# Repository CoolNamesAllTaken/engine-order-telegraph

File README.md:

# engine-order-telegraph
Ding! More doot, please.

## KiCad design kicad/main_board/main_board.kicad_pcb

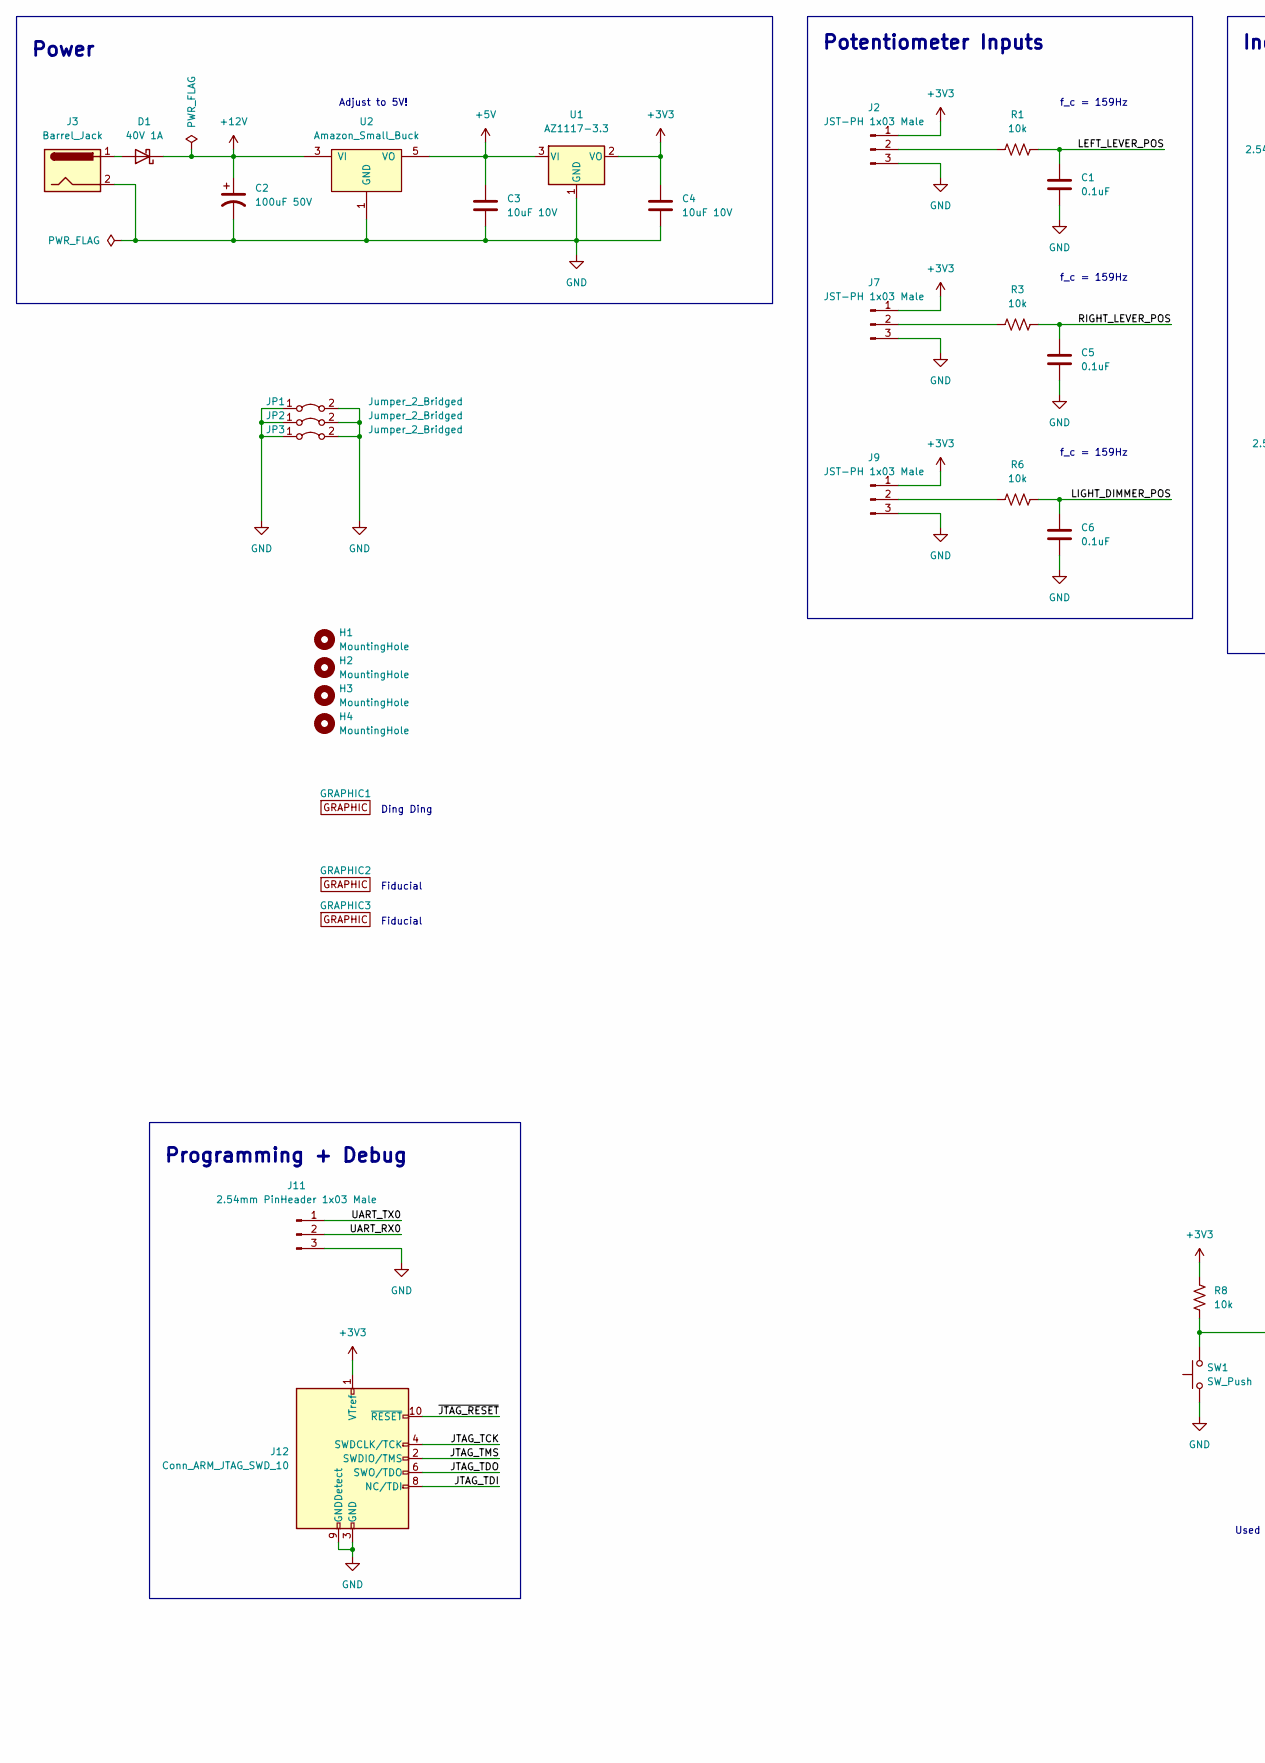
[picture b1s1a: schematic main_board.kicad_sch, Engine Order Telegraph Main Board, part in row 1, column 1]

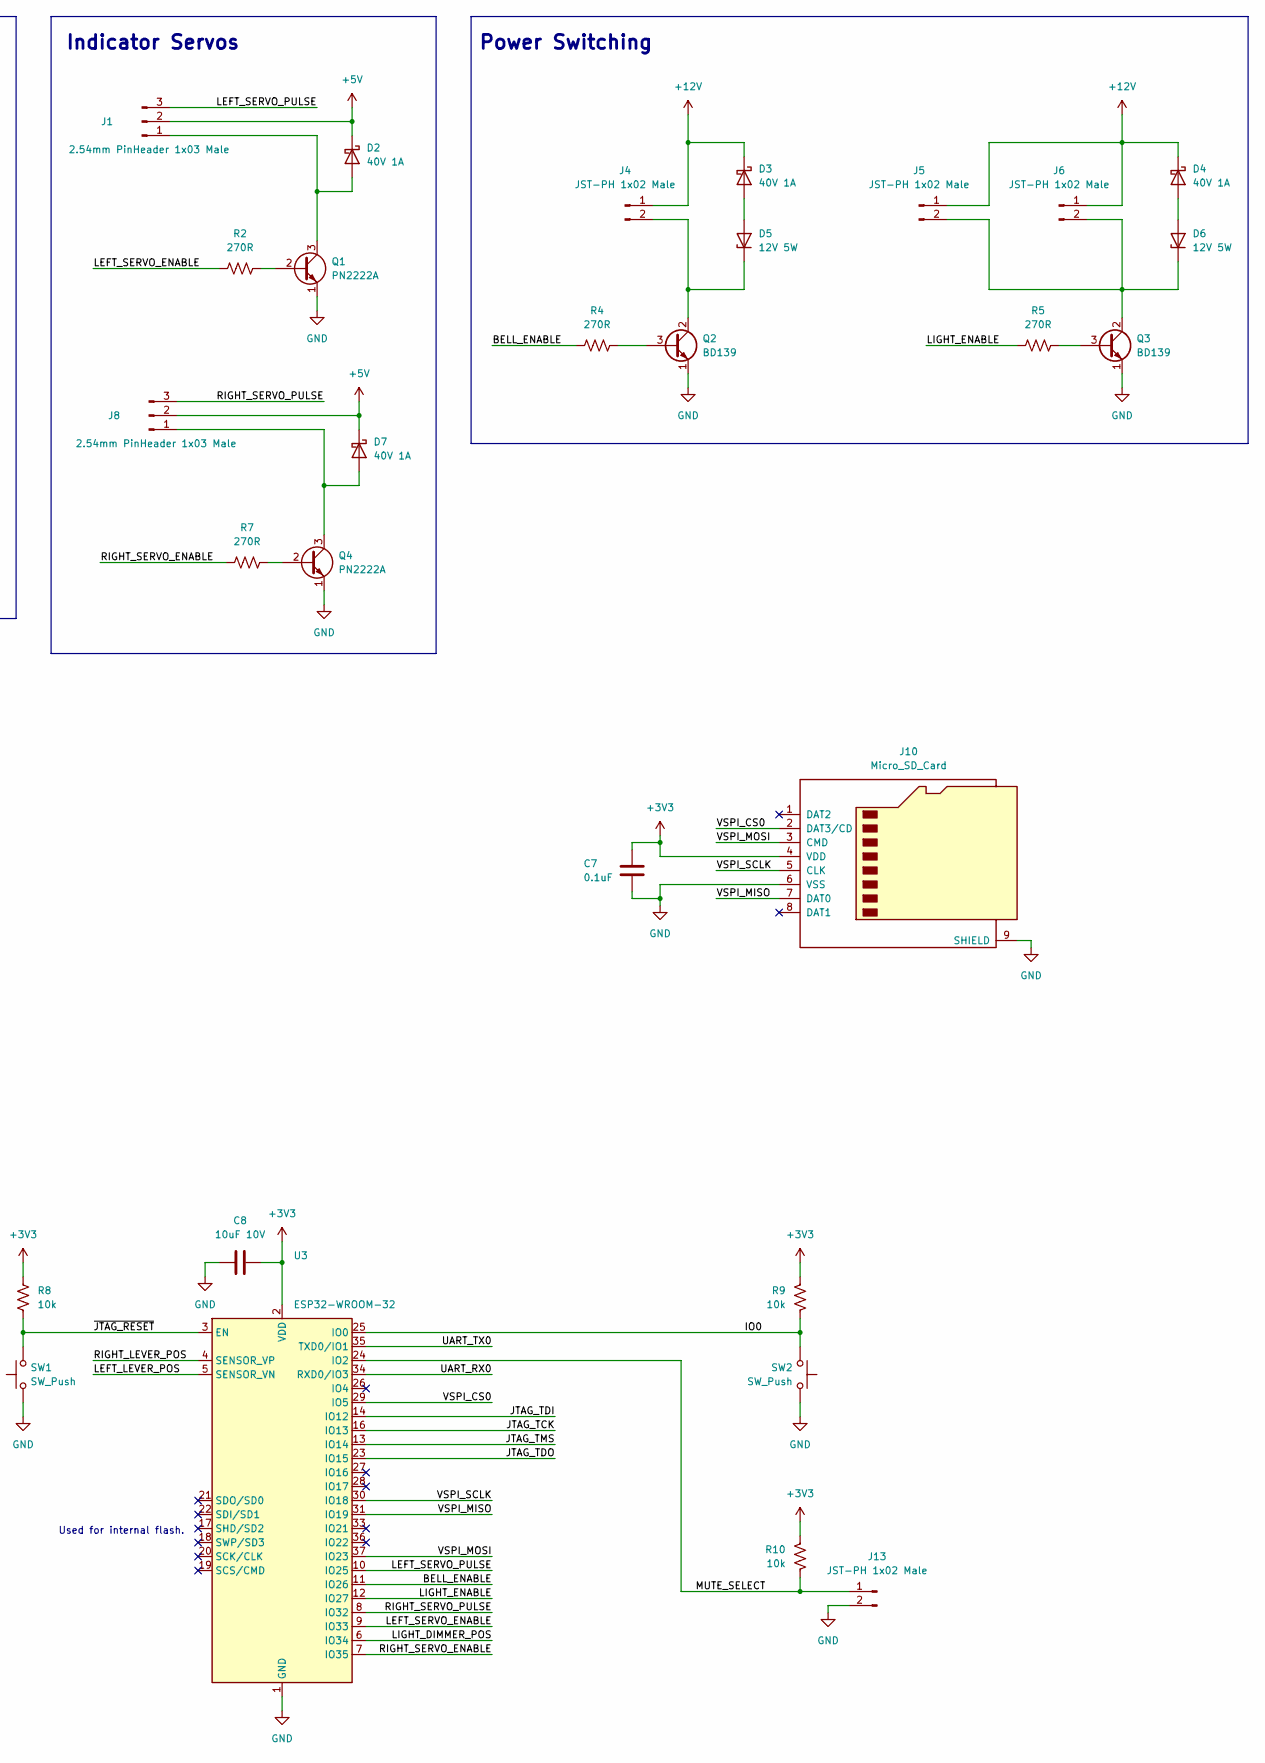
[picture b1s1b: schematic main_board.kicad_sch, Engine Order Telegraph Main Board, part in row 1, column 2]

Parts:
C1, C5, C6, C7: 0.1uF; C_0805_2012Metric
C2: 100uF 50V; CP_Radial_D8.0mm_P3.50mm
C3, C4, C8: 10uF 10V; C_0805_2012Metric
D1, D2, D3, D4, D7: 40V 1A; D_DO-41_SOD81_P7.62mm_Horizontal; MPN 1N5819
D5, D6: 12V 5W; D_DO-201AE_P12.70mm_Horizontal; MPN 1N5349
GRAPHIC1: Ding Ding!; ding_ding
GRAPHIC2, GRAPHIC3: Graphic; Fiducial_1mm_Mask2mm
H1, H2, H3, H4: MountingHole; MountingHole_3.2mm_M3
J1, J8: 2.54mm PinHeader 1x03 Male; PinHeader_1x03_P2.54mm_Horizontal
J2, J7, J9: JST-PH 1x03 Male; JST_PH_B3B-PH-K_1x03_P2.00mm_Vertical; MPN PH-3A
J3: Barrel_Jack; SOFNG_DC005-T20; MPN DC005-T20
J4, J5, J6, J13: JST-PH 1x02 Male; JST_PH_B2B-PH-K_1x02_P2.00mm_Vertical; MPN PH-2A
J10: Micro_SD_Card; SD_GCT-MEM2055-00-190-01-A
J11: 2.54mm PinHeader 1x03 Male; PinHeader_1x03_P2.54mm_Vertical
J12: Conn_ARM_JTAG_SWD_10; PinHeader_2x05_P1.27mm_Vertical_SMD; MPN 4048
JP1, JP2, JP3: Jumper_2_Bridged; R_0805_2012Metric
Q1, Q4: PN2222A; TO-92_Inline
Q2, Q3: BD139; TO-126-3_Horizontal_TabDown
R1, R3, R6, R8, R9, R10: 10k; R_0805_2012Metric
R2, R4, R5, R7: 270R; R_0805_2012Metric
SW1, SW2: SW_Push; SW_SPST_TL3342
U1: AZ1117-3.3; SOT-223-3_TabPin2
U2: Amazon_Small_Buck
U3: ESP32-WROOM-32

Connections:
+3V3: C4.1, C7.1, C8.2, J2.1, J7.1, J9.1, J10.4 (VDD), J12.1 (VTref), R8.1, R9.1, R10.2, U1.2 (VO), U3.2 (VDD)
+5V: C3.1, D2.1 (K), D7.1 (K), J1.2, J8.2, U1.3 (VI), U2.5 (VO), U2.6 (VO)
+12V: C2.1, D1.1 (K), D3.1 (K), D4.1 (K), J4.1, J5.1, J6.1, U2.3 (VI), U2.4 (VI)
/BELL_ENABLE: R4.1, U3.11 (IO26)
/IO0: R9.2, SW2.2, U3.25 (IO0)
/JTAG_TCK: J12.4 (SWDCLK/TCK), U3.16 (IO13)
/JTAG_TDI: J12.8 (NC/TDI), U3.14 (IO12)
/JTAG_TDO: J12.6 (SWO/TDO), U3.23 (IO15)
/JTAG_TMS: J12.2 (SWDIO/TMS), U3.13 (IO14)
/LEFT_LEVER_POS: C1.1, R1.2, U3.5 (SENSOR_VN)
/LEFT_SERVO_ENABLE: R2.1, U3.9 (IO33)
/LEFT_SERVO_PULSE: J1.3, U3.10 (IO25)
/LIGHT_DIMMER_POS: C6.1, R6.2, U3.6 (IO34)
/LIGHT_ENABLE: R5.1, U3.12 (IO27)
/MUTE_SELECT: J13.1, R10.1, U3.24 (IO2)
/RIGHT_LEVER_POS: C5.1, R3.2, U3.4 (SENSOR_VP)
/RIGHT_SERVO_ENABLE: R7.1, U3.7 (IO35)
/RIGHT_SERVO_PULSE: J8.3, U3.8 (IO32)
/UART_RX0: J11.2, U3.34 (RXD0/IO3)
/UART_TX0: J11.1, U3.35 (TXD0/IO1)
/VSPI_CS0: J10.2 (DAT3/CD), U3.29 (IO5)
/VSPI_MISO: J10.7 (DAT0), U3.31 (IO19)
/VSPI_MOSI: J10.3 (CMD), U3.37 (IO23)
/VSPI_SCLK: J10.5 (CLK), U3.30 (IO18)
/~JTAG_RESET: J12.10 (~RESET), R8.2, SW1.2, U3.3 (EN)
GND: C1.2, C2.2, C3.2, C4.2, C5.2, C6.2, C7.2, C8.1, J2.3, J3.2, J7.3, J9.3, J10.6 (VSS), J10.9 (SHIELD), J11.3, J12.3 (GND), J12.5 (GND), J12.9 (GNDDetect), J13.2, JP1.1 (A), JP1.2 (B), JP2.1 (A), JP2.2 (B), JP3.1 (A), JP3.2 (B), Q1.1 (E), Q2.1 (E), Q3.1 (E), Q4.1 (E), SW1.1, SW2.1, U1.1 (GND), U2.1 (GND), U2.2 (GND), U2.7 (GND), U2.8 (GND), U3.1 (GND), U3.15 (GND), U3.38 (GND), U3.39 (GND)
unnamed: D1.2 (A), J3.1
unnamed: D2.2 (A), J1.1, Q1.3 (C)
unnamed: D3.2 (A), D5.2 (A)
unnamed: D4.2 (A), D6.2 (A)
unnamed: D5.1 (K), J4.2, Q2.2 (C)
unnamed: D6.1 (K), J5.2, J6.2, Q3.2 (C)
unnamed: D7.2 (A), J8.1, Q4.3 (C)
unnamed: J2.2, R1.1
unnamed: J7.2, R3.1
unnamed: J9.2, R6.1
unnamed: Q1.2 (B), R2.2
unnamed: Q2.3 (B), R4.2
unnamed: Q3.3 (B), R5.2
unnamed: Q4.2 (B), R7.2

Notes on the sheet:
Used for internal flash.
f_c = 159Hz
Fiducial
Power Switching
Ding Ding
Programming + Debug
Adjust to 5V!
Indicator Servos
Potentiometer Inputs
Power

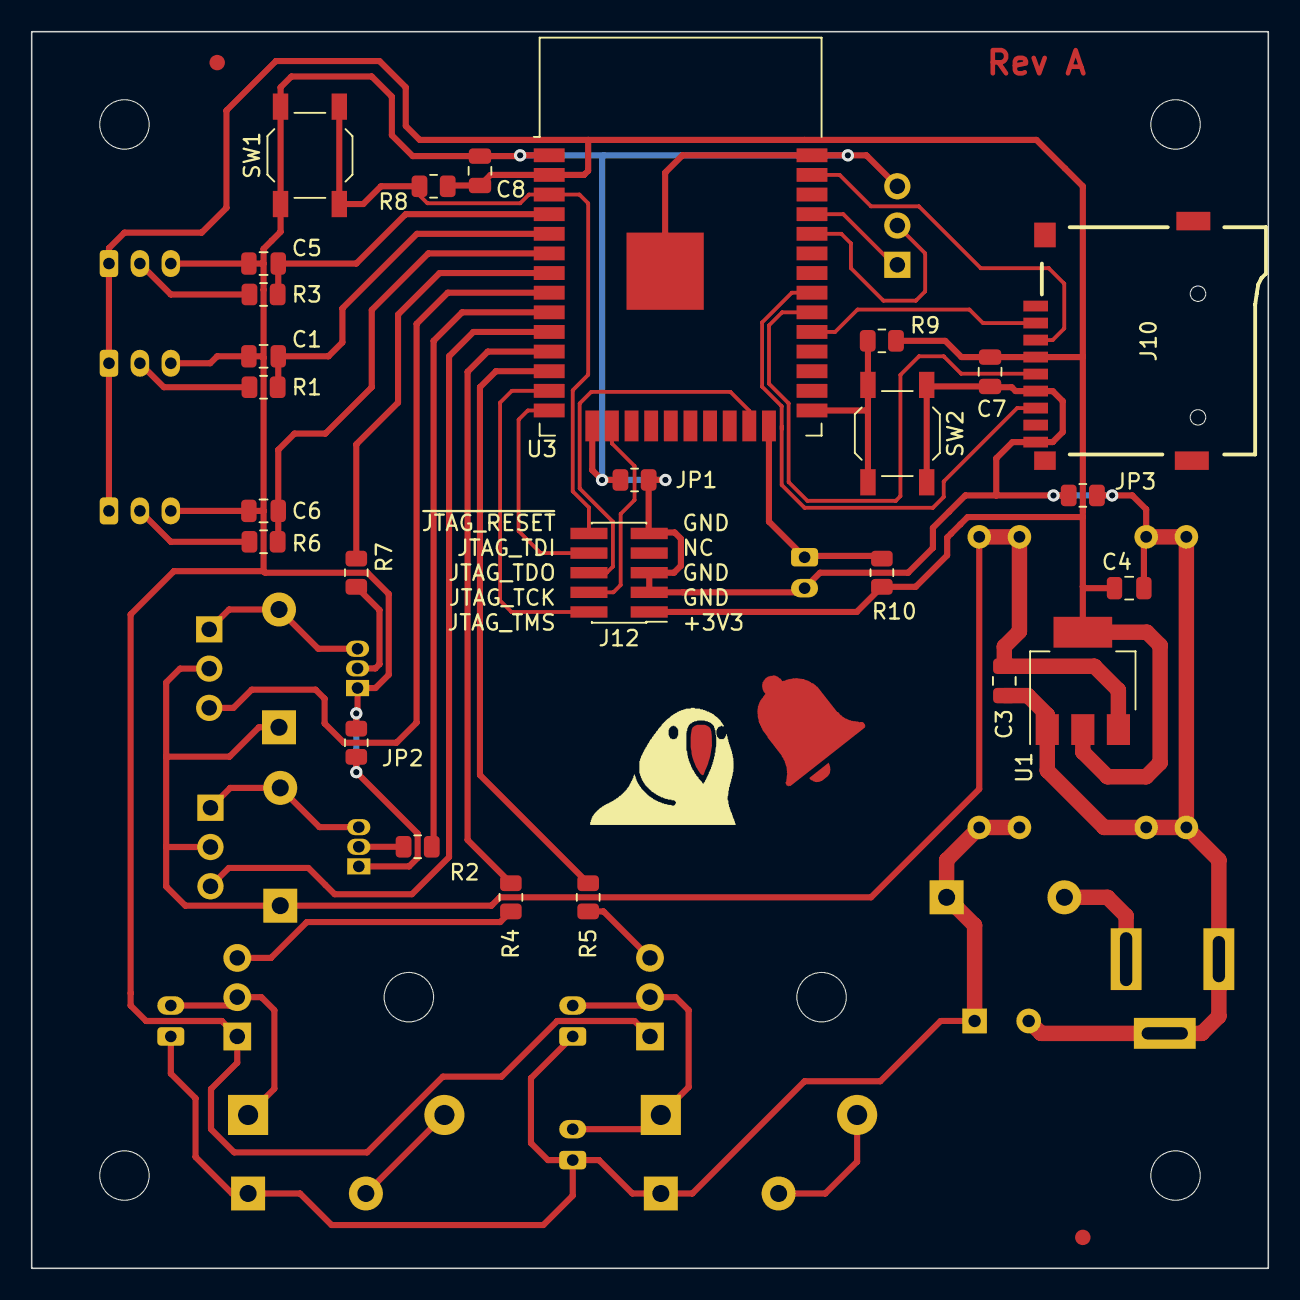
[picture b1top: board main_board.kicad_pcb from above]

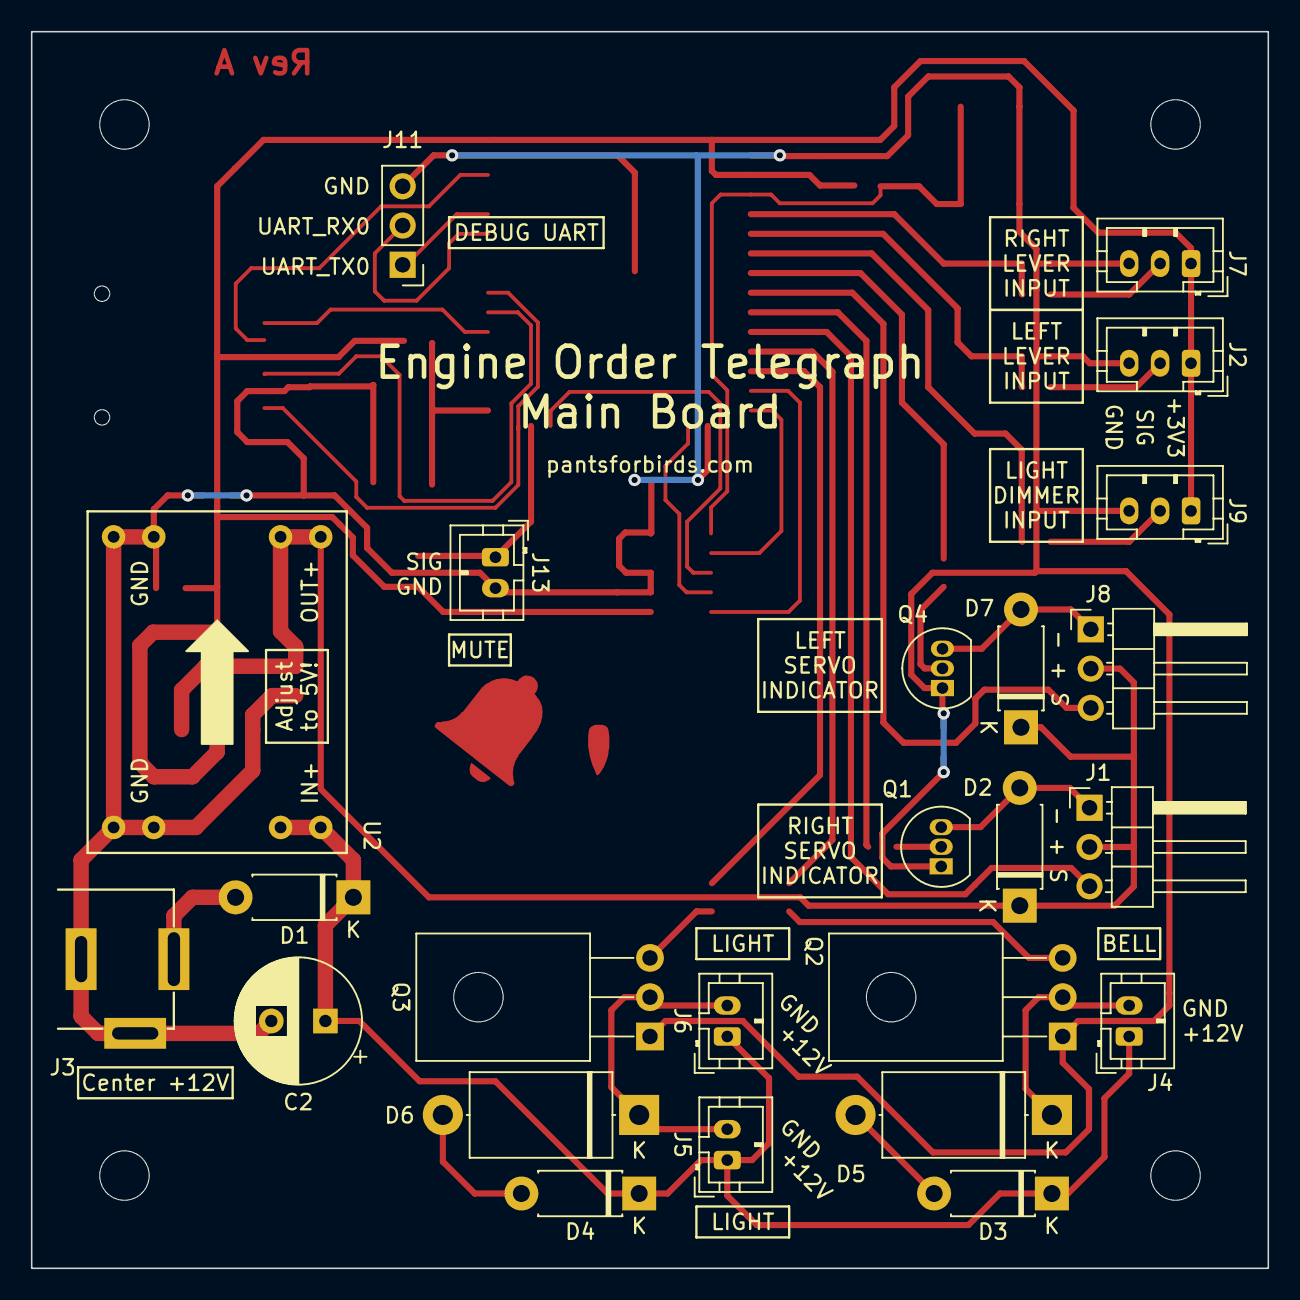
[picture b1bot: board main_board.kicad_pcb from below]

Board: 2 copper layers, 80.0 x 80.0 mm, 57 parts (24 on the bottom side), 40 nets.

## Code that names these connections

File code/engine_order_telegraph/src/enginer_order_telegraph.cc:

#include "engine_order_telegraph.hh"

#define ABS(x) ((x) > 0 ? (x) : (-(x)))

/** Public Functions **/

EngineOrderTelegraph::EngineOrderTelegraph(EngineOrderTelegraph::EngineOrderTelegraphConfig config_in)
    : config_(config_in) 
{

}

void EngineOrderTelegraph::Init() {
    // Set up digital inputs.
    pinMode(config_.mute_select_pin, INPUT);

    //  Set up digital outputs.
    pinMode(config_.bell_enable_pin, OUTPUT);
    pinMode(config_.light_enable_pin, OUTPUT);

    // Set up servos.
    pinMode(config_.left_servo_enable_pin, OUTPUT);
    left_servo_.attach(config_.left_servo_pulse_pin);
    pinMode(config_.right_servo_enable_pin, OUTPUT);
    right_servo_.attach(config_.right_servo_pulse_pin);

    // Set up analog inputs.
    // Nothing required here for ESP32.

    // Ring bell when done initializing.
    RingBell(2);
}

void EngineOrderTelegraph::Update() {
    
    Serial.printf("Left Lever: %dcts(%d) Right Lever: %dcts(%d) Dimmer: %d Dings: %d\r\n", 
        left_lever_position_counts,
        left_lever_position,
        right_lever_position_counts,
        right_lever_position,
        analogRead(config_.light_dimmer_pos_pin),
        num_pending_bell_rings
    );
    // Loopback mode for testing.
    ReadLeverPositions();
    UpdateBell();
    UpdateServos();
    UpdateLight();
}

void EngineOrderTelegraph::DeInit() {
    left_servo_.detach();
    right_servo_.detach();
}

void EngineOrderTelegraph::RingBell(uint16_t num_rings=1) {
    num_pending_bell_rings += num_rings;
}

/** Private Functions **/

/**
 * @brief Checks position of both levers and enqueues bell rings if necessary. Called by Update().
*/
void EngineOrderTelegraph::ReadLeverPositions() {
    int old_left_lever_position = left_lever_position;
    int old_left_lever_position_counts = old_left_lever_position*kLeftLeverStepCounts + kLeftLeverStartCounts;
    left_lever_position_counts = 
        kLeverFilterOldPosWeight*left_lever_position_counts/kLeverFilterTotalWeight 
        + kLeverFilterNewPosWeight*analogRead(config_.left_lever_pos_pin)/kLeverFilterTotalWeight;
    // left_lever_position_counts = analogRead(config_.left_lever_pos_pin);
    if (
        left_lever_position_counts < old_left_lever_position_counts + kLeftLeverStepCounts/2 - kLeverStepHysteresisCounts ||
        left_lever_position_counts > old_left_lever_position_counts - kLeftLeverStepCounts/2 + kLeverStepHysteresisCounts
    ) {
        // Only allow lever position update if hysteresis is overcome.
        left_lever_position = (left_lever_position_counts - kLeftLeverStartCounts + kLeftLeverStepCounts/2) / kLeftLeverStepCounts;
        volatile int absDeltaRings = ABS(left_lever_position-old_left_lever_position);
        RingBell(absDeltaRings);
    }

    int old_right_lever_position = right_lever_position;
    int old_right_lever_position_counts = old_right_lever_position*kRightLeverStepCounts + kRightLeverStartCounts;
    right_lever_position_counts = 
        kLeverFilterOldPosWeight*right_lever_position_counts/kLeverFilterTotalWeight
        + kLeverFilterNewPosWeight*analogRead(config_.right_lever_pos_pin)/kLeverFilterTotalWeight;
    // right_lever_position_counts = analogRead(config_.right_lever_pos_pin);
    if (
        right_lever_position_counts > old_right_lever_position_counts + kRightLeverStepCounts/2 + kLeverStepHysteresisCounts ||
        right_lever_position_counts < old_right_lever_position_counts - kRightLeverStepCounts/2 - kLeverStepHysteresisCounts
    ) {
        // Only allow lever position update if hysteresis is overcome.
        right_lever_position = (right_lever_position_counts - kRightLeverStartCounts + kRightLeverStepCounts/2) / kRightLeverStepCounts;
        volatile int absDeltaRings = ABS(right_lever_position-old_right_lever_position);
        RingBell(absDeltaRings);
    }
}

/**
 * @brief Updates the bell plunger to extend / retract if necessary to ring the bell. Called by Update().
*/
void EngineOrderTelegraph::UpdateBell() {
    
    muted_ = digitalRead(config_.mute_select_pin);
    if (muted_) {
        num_pending_bell_rings = 0; // Clear all pending rings if muted.
    }

    uint32_t current_timestamp_ms = millis();
    if (bell_plunger_down_ && (current_timestamp_ms - last_bell_ring_timestamp_ms_ > kBellPlungerDownIntervalMs)) {
        // Bell plunger is currently depressed, and it's time to retract it.
        digitalWrite(config_.bell_enable_pin, 0);
        bell_plunger_down_ = false;
    }
    else if (
        // Could add a mute check here if we thought num_pending_bell_rings might get modified after the initial mute check.
        num_pending_bell_rings > 0 && 
        current_timestamp_ms - last_bell_ring_timestamp_ms_ > kMinBellRingIntervalMs
    ) {
        last_bell_ring_timestamp_ms_ = current_timestamp_ms;
        digitalWrite(config_.bell_enable_pin, 1);
        bell_plunger_down_ = true;
        num_pending_bell_rings--;
    }
}

/**
 * @brief Moves the servos as required, and powers them down when they're not in use to keep them quiet. Called by Update().
*/
void EngineOrderTelegraph::UpdateServos() {
    if (left_servo_position != left_servo_last_written_position || right_servo_position != right_servo_last_written_position) {
        // Servos need to move!
        // Enable the servos.
        last_servo_move_timestamp_ms_ = millis();
        servos_enabled_ = true;
        digitalWrite(config_.left_servo_enable_pin, 1);
        digitalWrite(config_.right_servo_enable_pin, 1);

        // Convert positions to degrees and write to the servos.
        left_servo_.write(kServoEndDegrees - left_servo_position*kServoPositionIncrementDegrees);
        right_servo_.write(right_servo_position*kServoPositionIncrementDegrees + kServoStartDegrees);

        // Update the last written servo positions so we don't come back here till the desired position changes.
        left_servo_last_written_position = left_servo_position;
        right_servo_last_written_position = right_servo_position;

    } else if (servos_enabled_ && millis() > last_servo_move_timestamp_ms_ + kServoMoveIntervalMs) {
        // Time to turn off the servos, they've had enough time to move.
        servos_enabled_ = false;
        digitalWrite(config_.left_servo_enable_pin, 0);
        digitalWrite(config_.right_servo_enable_pin, 0);
    }
    
}

/**
 * @brief Updates the light as required.
*/
void EngineOrderTelegraph::UpdateLight() {
    light_brightness_ = analogRead(config_.light_dimmer_pos_pin) * kLightBrightnessMaxCounts / kLightDimmerMaxCounts;
     analogWrite(config_.light_enable_pin, light_brightness_);
}

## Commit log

2022-05-25 Main board Rev A
2023-11-11 Upload old changes
2023-11-11 Save progress before scissor mech
2023-11-13 Add index retainer and bell bracket
2023-11-20 Fix stupid macro issues
2023-11-28 Add hysteresis for lever position updates
2023-12-03 Fix hysteresis
2023-12-09 Add new 3d print files, fix lever hysteresis
